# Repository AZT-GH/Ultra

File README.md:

# AZUltra

Copyright © 2026 Adam Zembrzuski

Licensed under the TAPR Open Hardware License (www.tapr.org/OHL)
A full copy of the TAPR Open Hardware License is available in license.txt

<hr>

AZUltra is a periodic buzzer designed for space-constrained environments. Applications include warning alerts or sleep prevention. It is primarily a testbed for CH32V005 integration in my future projects.

View the project entirely in your browser on KiCanvas - https://kicanvas.org/?repo=https%3A%2F%2Fgithub.com%2FAZT-GH%2FUltra%2Ftree%2Fmain%2FGH_UPLOAD%2FAZUltra

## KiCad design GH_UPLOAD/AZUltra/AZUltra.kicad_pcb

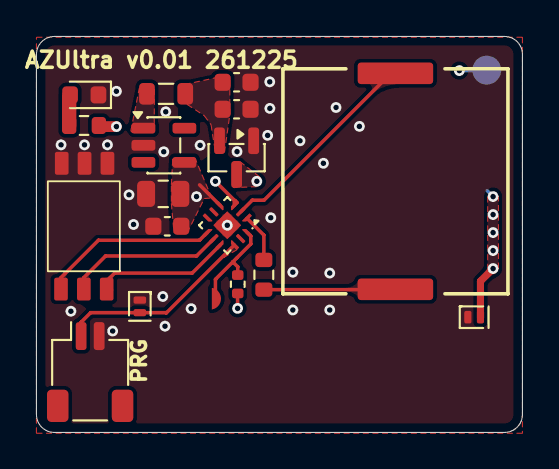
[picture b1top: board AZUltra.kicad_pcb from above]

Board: 4 copper layers, 27.0 x 22.0 mm, 18 parts (1 on the bottom side), 15 nets.

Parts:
BT1: CR2032; BatteryHolder_Keystone_3034_1x20mm
BZ1: KLJ1230
C2: 4.7μF; C_0603_1608Metric
C3, C5: 100nF; C_0603_1608Metric
C4: 22μF; C_0805_2012Metric
D1: LED; LED_0603_1608Metric
D2, D3: AQ1250-01ETG; D_SOD-882_DFN1006-2_TVS
J1: JST_SH_SM02B-SRSS-TB_1x02-1MP_P1.00mm_Horizontal
L1: 2.2μH; L_0805_2012Metric
Q1: SSM3J338R,LF; SOT-23
R1: 2K2; R_0603_1608Metric
R2: 220R; R_0603_1608Metric
R3: 100K; R_0402_1005Metric
SW1: SW_DIP_x03; SMXMS-03K-TR
U1: TPS613222ADBV; SOT-23-5
U2: CH32V005; IDT_QFN-12-1EP_2x2mm_P0.5mm_EP1.1x1.1mm

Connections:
+5V: C4.1, C5.1, R3.1, U1.4 (VOUT), U2.4 (VDD)
+BATT1: BT1.1 (+), D2.2 (K), Q1.3 (D)
/SWIO: D3.2 (K), J1.1, U2.10 (SWIO)
GND: BT1.2 (-), C2.2, C3.2, C4.2, C5.2, D1.1 (K), D2.1 (A), D3.1 (A), J1.2, Q1.1 (G), SW1.4, SW1.5, SW1.6, U1.2 (GND), U2.13 (VSS)
unnamed: BZ1.1 (+), R2.1
unnamed: BZ1.2 (-), U2.2 (TIM1_CH2N)
unnamed: D1.2 (A), R1.1
unnamed: R3.2, U2.12 (RST)
unnamed: C2.1, C3.1, L1.1, Q1.2 (S)
unnamed: L1.2, U1.1 (SW)
unnamed: R2.2, U2.1 (TIM1_CH2)
unnamed: SW1.3, U2.7 (PC4)
unnamed: SW1.2, U2.8 (PC6)
unnamed: SW1.1, U2.9 (PC7)
unnamed: R1.2, U2.3 (PD0)

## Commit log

2026-02-10 Project Bulk Upload
2026-02-10 Enhance README with image and KiCanvas link
    Added project image and link to KiCanvas for online viewing.
2026-02-10 Update README with copyright and license details
    Added copyright and licensing information to README.
2026-02-10 Update README with AZUltra description
    Added a brief description of AZUltra and its applications.
2026-02-10 Add TAPR Open Hardware License v1.0
    Added the TAPR Open Hardware License version 1.0 to the project.
2026-02-10 Rename project from Ultra to AZUltra
2026-02-10 Design Review Draft Upload
2026-02-10 Update schematic
2026-02-10 Update Schematic
    Actually new schematic uploaded this time
2026-02-10 Schematic reuplaod
2026-02-10 Update KiCanvas project link in README
2026-02-11 Update review
